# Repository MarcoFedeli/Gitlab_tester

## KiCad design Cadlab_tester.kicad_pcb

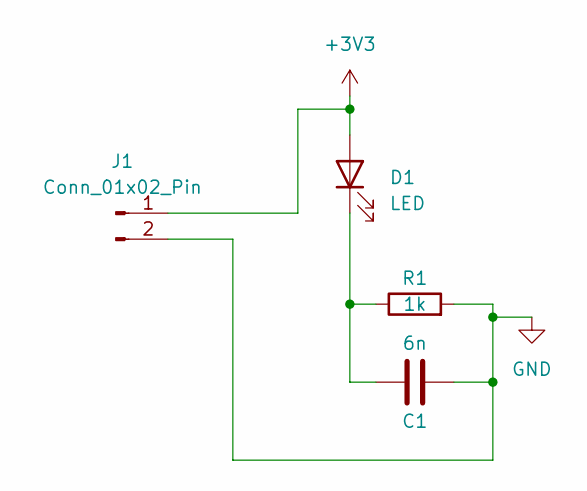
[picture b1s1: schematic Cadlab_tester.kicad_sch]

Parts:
C1: 6n; C_1812_4532Metric
D1: LED; LED_2512_6332Metric
J1: Conn_01x02_Pin; Molex_Micro-Fit_3.0_43650-0221_1x02_P3.00mm_Vertical
R1: 1k; R_MELF_MMB-0207

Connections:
+3V3: D1.2 (A), J1.1
GND: C1.2, J1.2, R1.2
unnamed: C1.1, D1.1 (K), R1.1

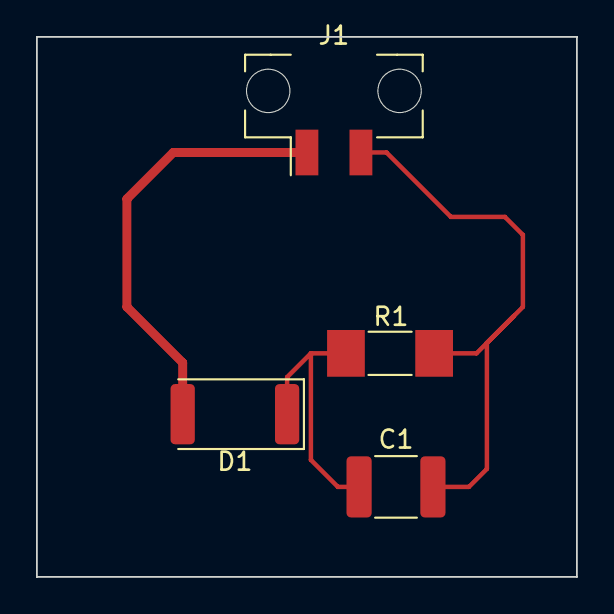
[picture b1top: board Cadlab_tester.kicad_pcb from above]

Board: 2 copper layers, 30.0 x 30.0 mm, 4 parts (0 on the bottom side), 3 nets.

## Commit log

2024-01-11 Progetto vuoto
2024-01-11 Rev1
2024-01-11 Schematico aggiornato
2024-01-11 Rev2
